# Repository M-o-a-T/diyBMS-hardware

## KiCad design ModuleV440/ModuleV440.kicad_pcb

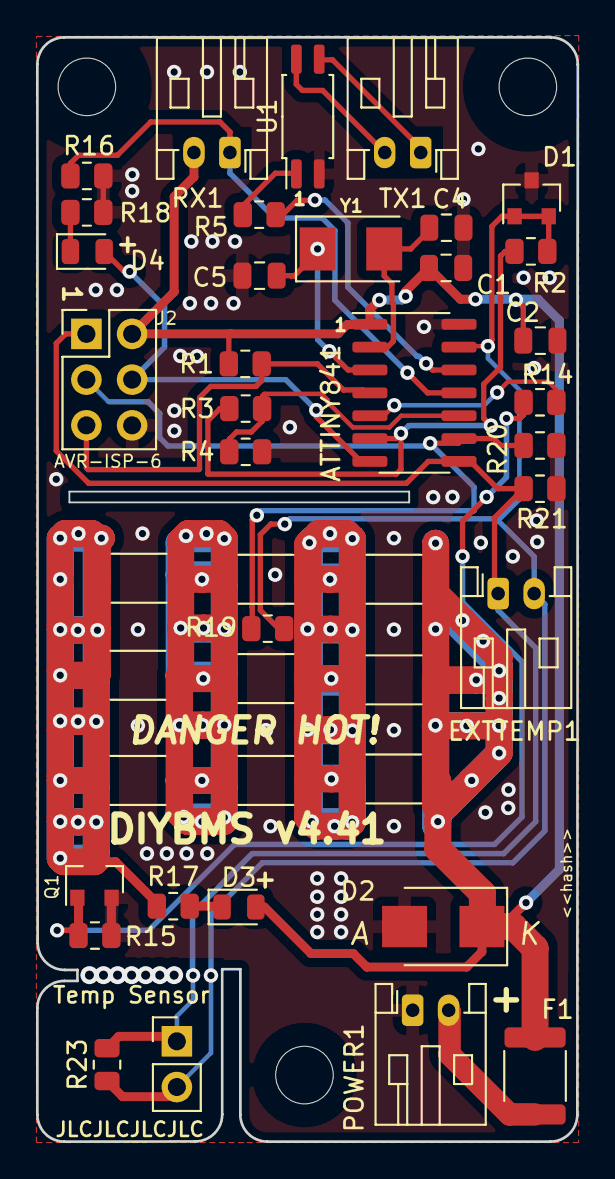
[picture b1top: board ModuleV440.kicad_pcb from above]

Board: 2 copper layers, 30.0 x 61.3 mm, 42 parts (0 on the bottom side), 24 nets.

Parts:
ATTINY841: ATtiny841-SSU; SOIC-14_3.9x8.7mm_P1.27mm
C1: 100nF; C_0805_2012Metric
C2: 1uF; C_0805_2012Metric
C4, C5: 22pF; C_0805_2012Metric
D1: AZ432ANTR-E1; SOT-23
D2: SMBJ5.0A; D_SMB
D3: Red; LED_0805_2012Metric
D4: Blue; LED_0805_2012Metric
EXTTEMP1: Ext Temp Sensor; JST_PH_S2B-PH-K_1x02_P2.00mm_Horizontal
F1: mSMD150; Fuse_1812_4532Metric
J2: AVR-ISP-6; Pin_Header_Straight_2x03_Pitch2.54mm
POWER1: Battery; JST_PH_S2B-PH-K_1x02_P2.00mm_Horizontal
Q1: AO3400A; SOT-23
R1, R15, R20, R21: 10KOHMS; R_0805_2012Metric
R2: 1KOHMS; R_0805_2012Metric
R3: 6.8K; R_0805_2012Metric
R4: 2.7K; R_0805_2012Metric
R5: 220 OHMS; R_0805_2012Metric
R6, R8, R12, R22, R24, R25, R26, R29, R30: 3.3OHM 3/4W; R_2010_5025Metric
R14: 510OHMS; R_0805_2012Metric
R16, R17, R18: 2.2KOHMS; R_0805_2012Metric
R19, R23: CMFB103F3950FANT; R_0805_2012Metric
REMOTE1: Ext Temp Sensor; PinHeader_1x02_P2.54mm_Vertical
RX1: RX Connector; JST_PH_S2B-PH-K_1x02_P2.00mm_Horizontal
TX1: TX Connector; JST_PH_S2B-PH-K_1x02_P2.00mm_Horizontal
U1: EL3H7(B)(TA)-G; SOP-4_4.4x2.6mm_P1.27mm
Y1: 8MHZ Ceramic Resonator; Crystal_SMD_5032-2pin_5.0x3.2mm

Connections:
DUMP_LOAD_ENABLE: ATTINY841.5 (PB2), R14.2
ENABLE: ATTINY841.6 (PA7), R2.1, R3.1
GND: ATTINY841.14 (GND), C1.2, C2.2, C4.2, C5.2, D1.3 (A), D2.2 (A2), J2.6 (GND), POWER1.1, Q1.2 (S), R4.2, R15.2, R16.1, R18.1, R20.2, R21.2, U1.2
MISO: ATTINY841.8 (PA5), EXTTEMP1.1, J2.1 (MISO), R21.1, R23.2, REMOTE1.1
unnamed: ATTINY841.10 (PA3), R3.2, R4.1
unnamed: ATTINY841.2 (XTAL1/PB0), C4.1, Y1.2
unnamed: ATTINY841.3 (XTAL2/PB1), C5.1, Y1.1
unnamed: ATTINY841.7 (PA6), D4.2 (A), J2.4 (MOSI)
unnamed: ATTINY841.4 (~RESET/PB3), J2.5 (~RST), R1.2
unnamed: F1.2, POWER1.2
unnamed: Q1.1 (G), R14.1, R15.1
unnamed: Q1.3 (D), R12.2, R17.1, R29.2, R30.2
unnamed: R5.1, U1.1
unnamed: D3.1 (K), R17.2
unnamed: D4.1 (K), R18.2
unnamed: R6.2, R8.1, R22.2, R24.2, R25.1, R26.1
unnamed: R8.2, R12.1, R25.2, R26.2, R29.1, R30.1
unnamed: TX1.1, U1.3
unnamed: TX1.2, U1.4
RXD0: ATTINY841.11 (PA2), R16.2, RX1.1
SCK: ATTINY841.9 (PA4), J2.3 (SCK), R19.2, R20.1
TXD0: ATTINY841.12 (PA1), R5.2
VCC: ATTINY841.1 (VCC), C1.1, C2.1, D2.1 (A1), D3.2 (A), F1.1, J2.2 (VCC), R1.1, R6.1, R22.1, R24.1, RX1.2
VREF: ATTINY841.13 (AREF/PA0), D1.1 (FB), D1.2 (K), EXTTEMP1.2, R2.2, R19.1, R23.1, REMOTE1.2

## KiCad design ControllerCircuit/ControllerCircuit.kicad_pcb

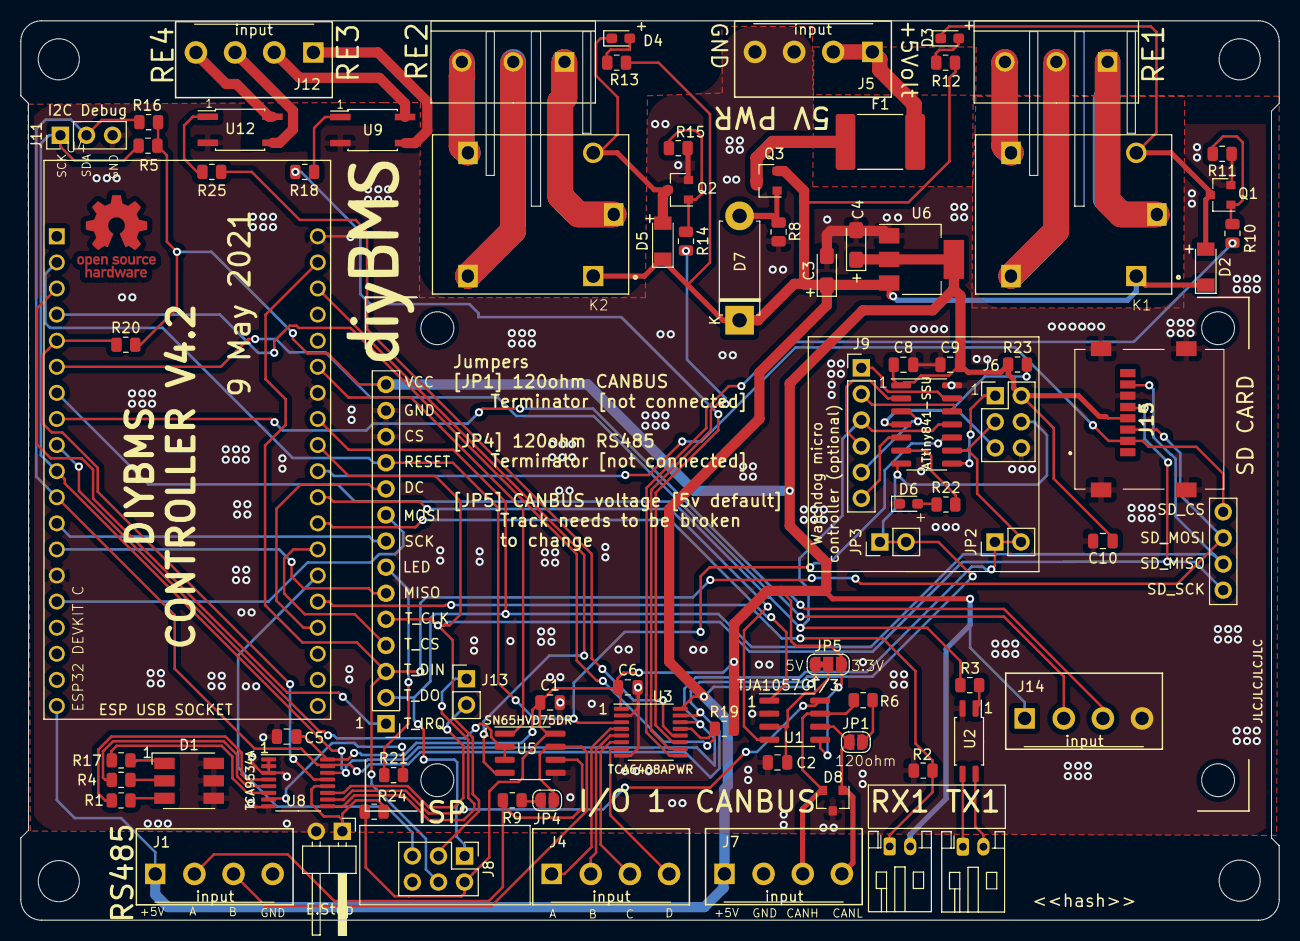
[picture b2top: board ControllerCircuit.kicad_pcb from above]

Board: 2 copper layers, 122.5 x 87.5 mm, 80 parts (0 on the bottom side), 88 nets.

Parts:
C1, C2, C5, C6, C8: 100nF; C_0805_2012Metric
C3, C4: 22uF 6.3V; CP_EIA-3216-18_Kemet-A_Pad1.58x1.35mm_HandSolder
C9, C10: 1uF; C_0805_2012Metric
D1: RGB; LED_RGB_5050-6
D2, D5: LL4148; D_MiniMELF
D3, D4, D6: YELLOW LED; LED_0603_1608Metric_Pad1.05x0.95mm_HandSolder
D7: D_Zener_Small; D_5W_P10.16mm_Horizontal
D8: NUP2105LT1G; SOT-23
F1: Fuse, 1.85A; Fuse_2920_7451Metric
J1, J4, J5, J7, J12, J14: ScrewTerminal; Terminal-Block_3.81_4P_LCSC_C395880
J2, J3: ScrewTerminal3Pin; Terminal-Block_5.0mm_3P-LCSC_C395850
J6: AVR-ISP-6; PinHeader_2x03_P2.54mm_Vertical
J8: 2x3 2.54mm IDC Connectors; PinHeader_2x03_P2.54mm_Vertical
J9: Conn_01x06_Female; PinHeader_1x06_P2.54mm_Vertical
J10: Conn_01x02_Female; PinHeader_1x02_P2.54mm_Horizontal
J11: Conn_01x03_Female; PinHeader_1x03_P2.54mm_Vertical
J13: Conn_01x02_Female; PinHeader_1x02_P2.54mm_Vertical
J15: Molex 0472192001; 0472192001
JP1, JP4: OptTermination; SolderJumper-2_P1.3mm_Open_RoundedPad1.0x1.5mm
JP2, JP3: Conn_01x02_Female; PinHeader_1x02_P2.54mm_Vertical
JP5: CANBUS Volt Select; SolderJumper-3_P1.3mm_Bridged12_RoundedPad1.0x1.5mm
K1, K2: SRD-05VDC-SL-C; RELAY_SRD-05VDC-SL-C
LCD1: LCD; TFTSPI_2_8_240x320_TOUCH
Q1, Q2: AO3400A; SOT-23
Q3: AO3401A; SOT-23
R1, R8: 100R; R_0805_2012Metric
R2, R5, R16: 2K2; R_0805_2012Metric
R3, R21, R22: 180R; R_0805_2012Metric
R4, R17: 300R; R_0805_2012Metric
R6, R9: 120R; R_0805_2012Metric
R10, R14, R18, R25: 220R; R_0805_2012Metric
R11, R15, R19, R20, R23, R24: 10K; R_0805_2012Metric
R12, R13: 560R; R_0805_2012Metric
RX1: Receive; JST_PH_S2B-PH-K_1x02_P2.00mm_Horizontal
TX1: Transmit; JST_PH_S2B-PH-K_1x02_P2.00mm_Horizontal
U1: TJA1057GT/3; SOIC-8_3.9x4.9mm_P1.27mm
U2: EL3H7(B)(TA)-G; SOP-4_4.4x2.6mm_P1.27mm
U3: TCA6408APWR; TSSOP-16_4.4x5mm_P0.65mm
U4: ESP32-DEVKITC-32D; MODULE_ESP32-DEVKITC-32D
U5: SN65HVD75DR; SOIC-8_3.9x4.9mm_P1.27mm
U6: AMS1117-3.3; SOT-223-3_TabPin2
U8: TCA9534A; TSSOP-16_4.4x5mm_P0.65mm
U9, U12: AQY212GSZ; SO-4_4.4x3.6mm_P2.54mm
U10: ATtiny841-SSU; SOIC-14_3.9x8.7mm_P1.27mm

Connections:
+3V3: C1.1, C4.1, C5.2, C6.1, C8.1, C9.2, C10.1, J6.2 (VCC), J8.2 (VCC), J14.1, J15.4 (VDD), JP5.3 (B), LCD1.14 (VCC), R5.2, R16.2, R19.2, R20.2, R23.1, R24.2, RX1.2, U1.5 (VIO), U3.1 (VCCI), U5.8 (VCC), U6.2 (VO), U8.16 (VDD), U10.1 (VCC)
+5V: F1.2, J5.1, J5.2
/AVRISP_RESET: J8.5 (~RST), U4.33 (IO0)
/BLUE_LED: R1.2, U8.4 (P0)
/CANBUS_RX: U1.4 (RXD), U4.30 (IO17)
/CANBUS_S: U1.8 (S), U8.10 (P5)
/CANBUS_TX: U1.1 (TXD), U4.31 (IO16)
/DISPLAY_DC: LCD1.10 (D/C), U4.35 (IO15)
/DISPLAY_LED: R21.2, U8.7 (P3)
/EXT_IO_A: J4.1, U3.4 (P0)
/EXT_IO_B: J4.2, U3.5 (P1)
/EXT_IO_C: J4.3, U3.6 (P2)
/EXT_IO_D: J4.4, U3.7 (P3)
/GREEN_LED: R17.2, U8.6 (P2)
/HSPI_CLK: LCD1.8 (SCK), U4.12 (IO14)
/HSPI_MISO: LCD1.6 (MISO), U4.13 (IO12)
/HSPI_MOSI: LCD1.9 (MOSI), U4.15 (IO13)
/IO2: R2.2, RX1.1, U4.34 (IO2)
/IO4: LCD1.4 (T_CS), U4.32 (IO4)
/IO5: J15.2 (CD/DAT3), LCD1.SD4 (SD_CS), U4.29 (IO5)
/IO21: U4.25 (IO21), U5.1 (R)
/IO22: U4.22 (IO22), U5.4 (D)
/IO25: U4.9 (IO25), U5.2 (RE), U5.3 (DE)
/IO26: J6.3 (SCK), J11.1, JP2.1, JP2.2, R5.1, U3.14 (SCL), U4.10 (IO26), U8.14 (SCL), U10.9 (PA4)
/IO27: J6.4 (MOSI), J11.2, JP3.1, JP3.2, R16.1, U3.15 (SDA), U4.11 (IO27), U8.15 (SDA), U10.7 (PA6)
/IO32: J9.3, R3.2, U4.7 (IO32), U10.11 (PA2)
/IO33: J14.3, U4.8 (IO33)
/IO34_INPUT: R20.1, U4.5 (IO34), U8.13 (~INT)
/IO35_INPUT: J14.2, U4.6 (IO35)
/IO36_INPUT: LCD1.1 (T_IRQ), U4.3 (SENSOR_VP)
/IO39_INPUT: R19.1, U3.13 (~INT), U4.4 (SENSOR_VN)
/RED_LED: R4.2, U8.5 (P1)
/RELAY1: R10.2, U3.9 (P4)
/RELAY2: R14.2, U3.10 (P5)
/RELAY3_SSR: R18.2, U3.11 (P6)
/RELAY4_SSR: R25.2, U3.12 (P7)
/RESET: LCD1.11 (RESET), U3.3 (~RESET), U4.2 (EN), U10.10 (PA3)
/VSPI_CLK: J8.3 (SCK), J15.5 (CLK), LCD1.5 (T_CLK), LCD1.SD1 (SD_SCK), U4.28 (IO18)
/VSPI_MISO: J8.1 (MISO), J15.7 (DAT0), LCD1.2 (T_DO), LCD1.SD2 (SD_MISO), U4.27 (IO19)
/VSPI_MOSI: J8.4 (MOSI), J15.3 (CMD), LCD1.3 (T_DIN), LCD1.SD3 (SD_MOSI), U4.21 (IO23)
FUSED5V: C3.1, D2.1 (K), D5.1 (K), D7.1 (K), J1.1, J7.1, JP5.1 (A), K1.A1, K2.A1, Q3.2 (S), R12.2, R13.2, U3.16 (VCCP), U4.19 (EXT_5V), U6.3 (VI)
GND: C1.2, C2.2, C3.2, C4.2, C5.1, C6.2, C8.2, C9.1, C10.2, D1.4 (BA), D1.5 (GA), D1.6 (RA), D6.1 (K), D8.3 (A), J1.4, J5.3, J5.4, J6.6 (GND), J7.2, J8.6 (GND), J10.2, J11.3, J14.4, J15.6 (VSS), J15.G1 (GND_1), J15.G2 (GND_2), J15.G3 (GND_3), J15.G4 (GND_4), LCD1.12 (CS), LCD1.13 (GND), Q1.2 (S), Q2.2 (S), R2.1, R8.2, R11.1, R15.1, U1.2 (GND), U2.2, U3.2 (ADDR), U3.8 (GND), U4.14 (GND1), U4.20 (GND3), U4.26 (GND2), U5.5 (GND), U6.1 (GND), U8.1 (A0), U8.2 (A1), U8.3 (A2), U8.8 (GND), U9.2, U10.14 (GND), U12.2
unnamed: C2.1, JP5.2 (C), U1.3 (VCC)
unnamed: D1.1 (RK), R17.1
unnamed: D1.2 (GK), R4.1
unnamed: D1.3 (BK), R1.1
unnamed: D2.2 (A), D3.1 (K), K1.A2, Q1.3 (D)
unnamed: D3.2 (A), R12.1
unnamed: D4.1 (K), D5.2 (A), K2.A2, Q2.3 (D)
unnamed: D4.2 (A), R13.1
unnamed: D6.2 (A), R22.1
unnamed: D7.2 (A), Q3.1 (G), R8.1
unnamed: D8.1 (K), J7.4, JP1.1 (A), U1.6 (CANL)
unnamed: D8.2 (K), J7.3, R6.2, U1.7 (CANH)
unnamed: F1.1, Q3.3 (D)
unnamed: J1.2, R9.1, U5.6 (A)
unnamed: J1.3, JP4.1 (A), U5.7 (B)
unnamed: J2.1, K1.COM
unnamed: J2.2, K1.NC
unnamed: J2.3, K1.NO
unnamed: J3.1, K2.COM
unnamed: J3.2, K2.NC
unnamed: J3.3, K2.NO
unnamed: J6.1 (MISO), U10.8 (PA5)
unnamed: J6.5 (~RST), R23.2, U10.4 (~RESET/PB3)
unnamed: J9.1, U10.13 (AREF/PA0)
unnamed: J9.2, U10.12 (PA1)
unnamed: J9.4, U10.2 (XTAL1/PB0)
unnamed: J9.5, U10.3 (XTAL2/PB1)
unnamed: J9.6, U10.5 (PB2)
unnamed: J10.1, R24.1, U8.12 (P7)
unnamed: J12.1, U9.3
unnamed: J12.2, U9.4
unnamed: J12.3, U12.3
unnamed: J12.4, U12.4
unnamed: J13.1, U8.9 (P4)
unnamed: J13.2, U8.11 (P6)
unnamed: JP1.2 (B), R6.1
unnamed: JP4.2 (B), R9.2
unnamed: Q1.1 (G), R10.1, R11.2
unnamed: Q2.1 (G), R14.1, R15.2
unnamed: R3.1, U2.1
unnamed: R18.1, U9.1
unnamed: LCD1.7 (LED), R21.1
unnamed: R22.2, U10.6 (PA7)
unnamed: R25.1, U12.1
unnamed: TX1.1, U2.3
unnamed: TX1.2, U2.4

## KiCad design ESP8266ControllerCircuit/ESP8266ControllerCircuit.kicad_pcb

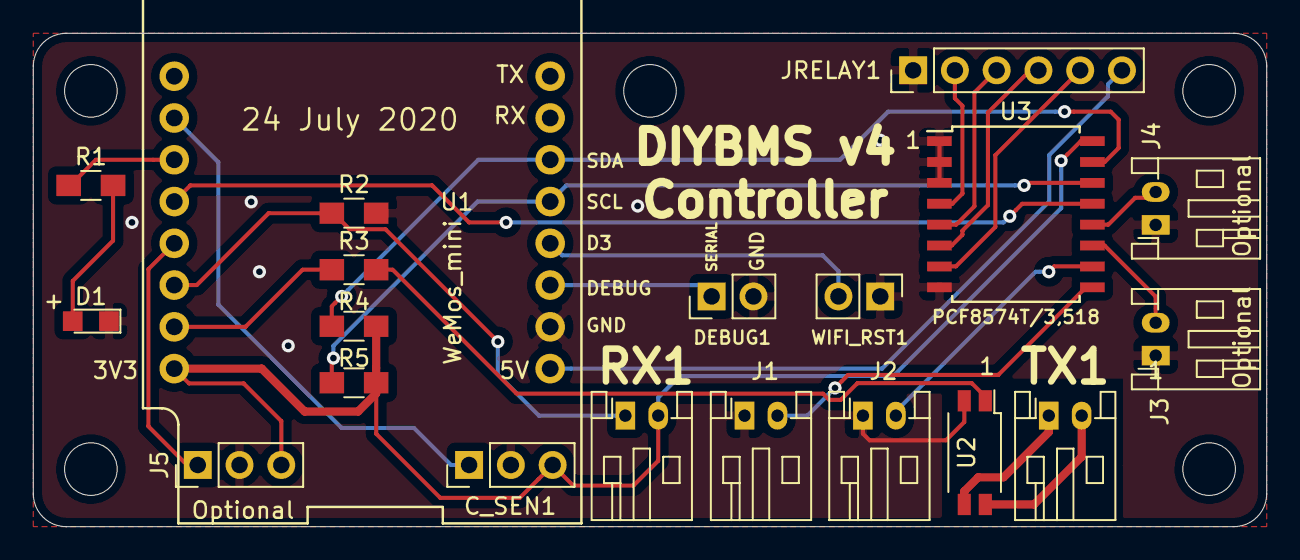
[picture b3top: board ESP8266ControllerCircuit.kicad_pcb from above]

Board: 2 copper layers, 75.0 x 30.0 mm, 20 parts (0 on the bottom side), 25 nets.

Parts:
C_SEN1: Current Sensor; Pin_Header_Straight_1x03_Pitch2.54mm
D1: COMMS; LED_0805
DEBUG1: Conn_01x02_Female; Pin_Header_Straight_1x02_Pitch2.54mm
J1, J2, J3, J4: Input; JST_PH_S2B-PH-K_02x2.00mm_Angled
J5: Optional; Pin_Header_Straight_1x03_Pitch2.54mm
JRELAY1: Conn_01x06_Male; Pin_Header_Straight_1x06_Pitch2.54mm
R1: 470R; R_0805_HandSoldering
R2, R4, R5: 4K7; R_0805_HandSoldering
R3: 220R; R_0805_HandSoldering
RX1: Receive; JST_PH_S2B-PH-K_02x2.00mm_Angled
TX1: Transmit; JST_PH_S2B-PH-K_02x2.00mm_Angled
U1: WeMos_mini; wemos-d1-mini-with-pin-header
U2: EL3H7(B)(TA)-G; SOP-4_4.4x2.8mm_Pitch1.27mm
U3: PCF8574T/3,518; SOIC-16W_7.5x10.3mm_Pitch1.27mm
WIFI_RST1: WIFI RST; Pin_Header_Straight_1x02_Pitch2.54mm

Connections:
+3V3: C_SEN1.3, J5.3, R4.1, R5.1, RX1.2, U1.16, U3.16
+5V: JRELAY1.6, U1.1
GND: C_SEN1.2, D1.1, DEBUG1.2, J1.1, J2.1, J3.1, J4.1, J5.2, JRELAY1.1, R2.1, U1.2, U2.2, U3.1, U3.2, U3.3, U3.8, WIFI_RST1.1
unnamed: C_SEN1.1, U1.10
unnamed: D1.2, R1.1
unnamed: DEBUG1.1, U1.3
unnamed: J1.2, U3.9
unnamed: J2.2, U3.10
unnamed: J3.2, U3.11
unnamed: J4.2, U3.12
unnamed: J5.1, U1.13
unnamed: JRELAY1.2, U3.4
unnamed: JRELAY1.3, U3.5
unnamed: JRELAY1.4, U3.6
unnamed: JRELAY1.5, U3.7
unnamed: R1.2, U1.11
unnamed: R2.2, RX1.1, U1.14
unnamed: R3.1, U2.1
unnamed: R3.2, U1.15
unnamed: TX1.1, U2.3
unnamed: TX1.2, U2.4
unnamed: U1.4, WIFI_RST1.2
PCFINT: U1.12, U3.13
SCL: R5.2, U1.5, U3.14
SDA: R4.2, U1.6, U3.15

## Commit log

2022-04-14 revert copyright change
2022-04-16 Moved dimensions to user.drawings layer
2022-04-16 More kicad6 migration
2022-04-16 Add hash to Module440 board
2022-04-16 Rename Module 440 to 441
2022-04-16 property sync, no changes
2022-04-16 Workflow: fix schematics' filenames
2022-04-16 spurious hole w/ overlapping courtyard

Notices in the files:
ControllerCircuit/ControllerCircuit.kicad_pcb:
©2019 to 2021 Stuart Pittaway
ESP8266ControllerCircuit/ESP8266ControllerCircuit.kicad_pcb:
©2019/2020 Stuart Pittaway
ModuleV440/ModuleV440.kicad_pcb:
©2019-2021
